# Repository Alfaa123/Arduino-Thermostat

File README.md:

# Arduino-Thermostat

This is a project to create a Arduino (or Arduino compatible) powered home thermostat. Version 2 PCB schematic and design is complete.

# Electrical Design

Version 2 has been updated and upgraded to use many SMD components. The board has shrunk, extra protections added and lots of the lessons learned from V1 were implemented as changes to V2.

## Power Section

This takes the 24v AC from the air handler transformer and rectifies it to create a high voltage DC bus. This is then smoothed and an LM2596 is used as a switching regulator to create a 3.3v supply.

Power for the feather is supplied via the 3.3v pin from the onboard voltage regulator.

The regulator can handle up to 3a of current and would be accurately described as "way overkill" for the power requirements of the low voltage section of this board. However, the LM2596 regulators are so simple and easy to effectively use (thanks TI!) that it was worth the extra cost to just have something "easy."

Because the circuitry in the air handler requires the relays to be switched on with the supplied 24v AC, it is routed down the board to supply the common terminal of the three main relays.

## Relay Drive Section

In order to drive the relays, small logic level MOSFETS are utilized with the feather board outputs acting as gate drivers for the three MOSFETs. The current requirements for the selected relays are very low and can easily be sunk by the selected MOSFETs.

## Inputs and Outputs

An Adafruit Feather HUZZAH ESP8266 will be used to run the thermostat. This was selected because it was cheap, easy to work with and included a WiFi stack (allowing for some internet connected thermostat features in the future). One limitation of the ESP8266 is the extremely limited IO compared to the Arduino Nano of the V1 design. This lead to lots of design challanges, including the use of the onboard ADC for ladder buttons to save IO.

The central feature of the V2 design is the inclusion of a 2.9 inch e-ink display instead of a standard LCD. This high resolution, low power display will be ideal for a thermostat as the display needs minimal updates during normal usage.

## Physical Outline

The physical outline of the board was designed to mimic my current thermostat. No mounting holes are included in the V2 design due to the success of the board edge mount that was used on the V1 design.

## Lessons Learned for V2

- ~~Arduino placement needs to be revised. Currently plugging in the USB cable is impossible without bending a cable and potentially damaging the Arduino. This is the biggest mistake.~~ **fixed on V2 design. USB connector points toward the board edge and is easy to access**
- ~~Screw terminal placement needs to be revised. Currently with the massive spacing, it required me to trim a lot of the insulation off of the 5 conductor cable in order to spread the wires out far enough to reach.~~ **fixed on V2 design. Screw terminals were moved much closer together and should make wiring the thermostat much easier**
- ~~More markings on the front of the PCB to show which screw terminal does what. Currently it requires me to open the schematic and board files to correctly wire the thermostat.~~ **fixed on V2 design. Board markings on the silkscreen should make wiring the thermostat much easier.**
- ~~More work should be done to minimize footprint. Currently, the thermostat is physically very large.~~ **fixed on V2 design. Board outline has shrunk to around 60% of the original size.**
- ~~A larger screen would be nice to fit more information. A dot matrix or OLED would be best.~~ **fixed on V2 design. e-ink display selected as high resolution and low power display.**
- ~~Smaller regulator section and relays would go a long way to making the board shrink.~~ **unchanged on V2 design. However, the capacitors were revised with shorter, higher quality parts, the regulator was changed to a surface mount version and the diode and inductor were swapped with physically smaller versions.**

# Programming

No V2 programming has been written yet.

## Required Libraries

TBD once V2 programming is underway

## Planned Future Development

- PID control or other method for better temperature control.
- Humidistat control mode
- Adjustable circ fan frequency
- Better menu system
- Filtering on the temperature sensor to prevent rapid cycling
- Cycling time limit to prevent compressor damage

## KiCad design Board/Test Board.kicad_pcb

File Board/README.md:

# Arduino-Thermostat

This is a project to create a arduino powered home thermostat. Currently the project is in the electrical design stage. Version 1 PCB schematic and design is complete.

# Electrical Design

The entire project was designed to be through hole for ease of assembly and troubleshooting. Perhaps in the future, a SMD version with a smaller footprint can be made once the electrical design is finalized.

## Power Section

This takes the 24v AC from the air handler transformer and rectifies it to create a higher voltage DC bus. This is then smoothed and an LM2596 is used as a switching regulator to create a 5.0v supply.

Power for the arduino is supplied via the 5v pin from the onboard voltage regulator.

The regulator can handle upto 3a of current and would be accurately described as "way overkill" for the power requirements of the low voltage section of this board. Once V1 is confirmed to be working, a redesign will be carried out that will allow a lower BOM cost and a physical design shrink.

Because the circuitry in the air handler requires the relays to be switched on with the supplied 24v AC, it is routed down the board to supply the common terminal of the three main relays.

## Relay Driver

A L293D Bipolar Motor Driver was chosen because it was readily available in DIP format, worked for the voltages required, had logic level inputs and had built in flyback diodes that allowed for less physical space usage at the expense of a higher BOM cost.

Additionally, due to the extra available output, the supply for the LCD backlight is switched with output 4.

## Inputs and Outputs

An arduino nano will be used to run the thermostat, ample GPIO meant that each physical button could have it's own DIO pin. Additionally, the LCD was able to be run directly in 4 bit parallel mode allowing for lower BOM cost and simpler electrical design.

The DHT11 may be swapped out with a DHT22 as they have the same footprint and the DHT 22 has a wider range of measurement.

## Physical Outline

The physical outline of the board was designed to mimic my current thermostat. 4 mounting holes were provided to allow for either wall mounting or a case.

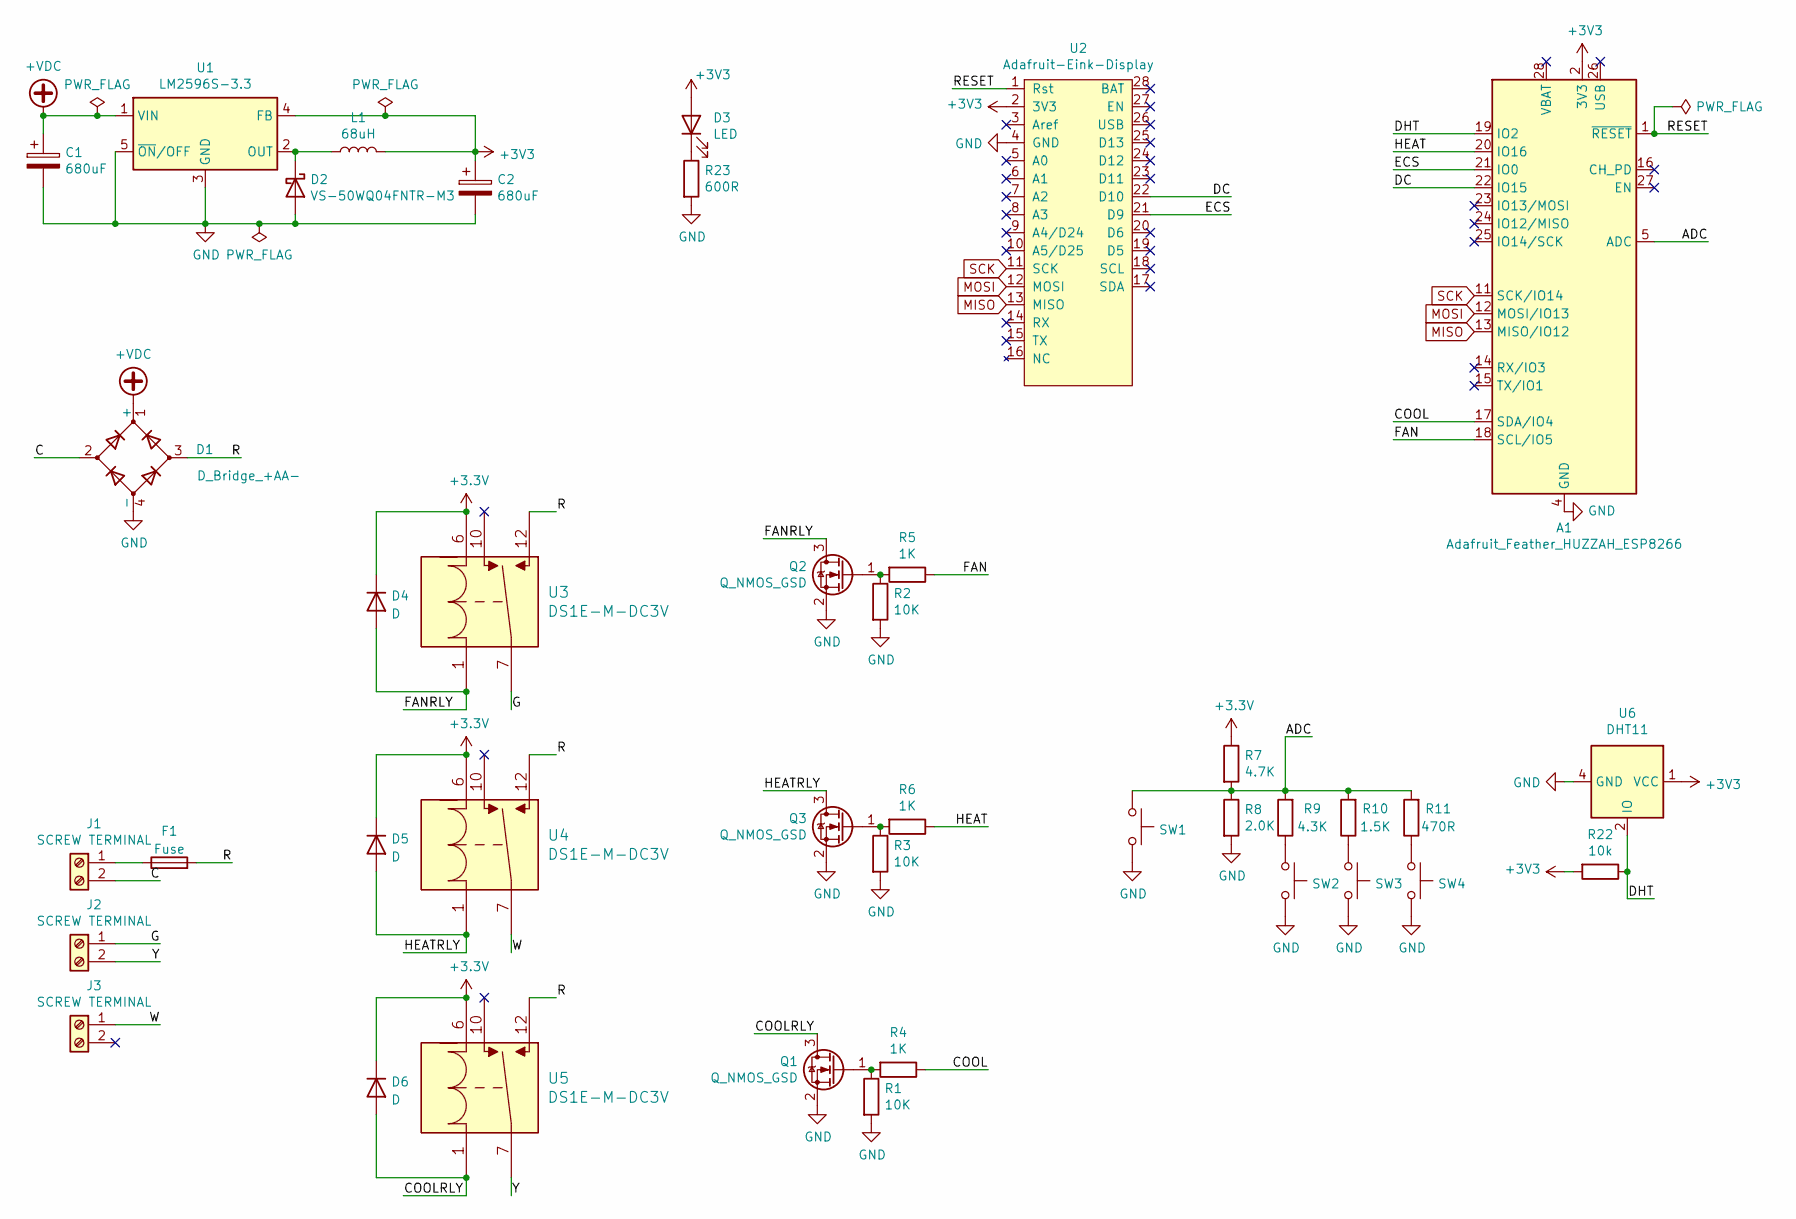
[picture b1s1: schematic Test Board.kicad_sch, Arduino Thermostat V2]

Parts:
A1: Adafruit_Feather_HUZZAH_ESP8266; Adafruit_Feather
C1, C2: 680uF; CP_Radial_D18.0mm_P7.50mm
D1: D_Bridge_+AA-; Diode Bridge 4-SMD
D2: VS-50WQ04FNTR-M3; TO-252-3_TabPin2
D3: LED; LED_1206_3216Metric_Pad1.42x1.75mm_HandSolder
D4, D5, D6: D; D_SMA_Handsoldering
F1: Fuse; Fuseholder_Blade_Mini_Keystone_3568
J1, J2, J3: SCREW TERMINAL; TerminalBlock_Phoenix_MKDS-1,5-2-5.08_1x02_P5.08mm_Horizont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
L1: 68uH; L_Radial_L16.1mm_W16.1mm_Px7.62mm_Py12.70mm_Pulse_LP-44
Q1, Q2, Q3: Q_NMOS_GSD; SOT-23
R1, R2, R3: 10K; R_1206_3216Metric
R4, R5, R6: 1K; R_1206_3216Metric
R7: 4.7K; R_1206_3216Metric
R8: 2.0K; R_1206_3216Metric
R9: 4.3K; R_1206_3216Metric
R10: 1.5K; R_1206_3216Metric
R11: 470R; R_1206_3216Metric
R22: 10k; R_1206_3216Metric
R23: 600R; R_1206_3216Metric
SW1, SW2, SW3, SW4: SW_Push; SW_PUSH_6mm_H5mm
U1: LM2596S-3.3; TO-263-5_TabPin3
U2: Adafruit-Eink-Display; Adafruit-eink-display
U3, U4, U5: DS1E-M-DC3V; DS1E-M-DC5V
U6: DHT11; DHT22-Horizontal

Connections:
+VDC: C1.1, D1.1 (+), U1.1 (VIN)
/ADC: A1.5 (ADC), R7.2, R8.1, R9.2, R10.2, R11.2, SW1.1
/C: D1.2, J1.2
/COOL: A1.17 (SDA/IO4), R4.1
/COOLRLY: D6.2 (A), Q1.3 (D), U5.1
/DC: A1.22 (IO15), U2.22 (D10)
/DHT: A1.19 (IO2), R22.1, U6.2 (IO)
/ECS: A1.21 (IO0), U2.21 (D9)
/FAN: A1.18 (SCL/IO5), R5.1
/FANRLY: D4.2 (A), Q2.3 (D), U3.1
/G: J2.1, U3.7
/HEAT: A1.20 (IO16), R6.1
/HEATRLY: D5.2 (A), Q3.3 (D), U4.1
/R: D1.3, F1.2, U3.12, U4.12, U5.12
/RESET: A1.1 (~RESET), U2.1 (Rst)
/W: J3.1, U4.7
/Y: J2.2, U5.7
GND: A1.4 (GND), C1.2, C2.2, D1.4 (-), D2.2 (A), Q1.2 (S), Q2.2 (S), Q3.2 (S), R1.2, R2.2, R3.2, R8.2, R23.2, SW1.2, SW2.2, SW3.2, SW4.2, U1.3 (GND), U1.5 (~ON/OFF), U2.4 (GND), U6.4 (GND)
MISO: A1.13 (MISO/IO12), U2.13 (MISO)
MOSI: A1.12 (MOSI/IO13), U2.12 (MOSI)
unnamed: D2.1 (K), L1.1, U1.2 (OUT)
unnamed: D3.1 (K), R23.1
unnamed: F1.1, J1.1
unnamed: Q1.1 (G), R1.1, R4.2
unnamed: Q2.1 (G), R2.1, R5.2
unnamed: Q3.1 (G), R3.1, R6.2
unnamed: R9.1, SW2.1
unnamed: R10.1, SW3.1
unnamed: R11.1, SW4.1
SCK: A1.11 (SCK/IO14), U2.11 (SCK)

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
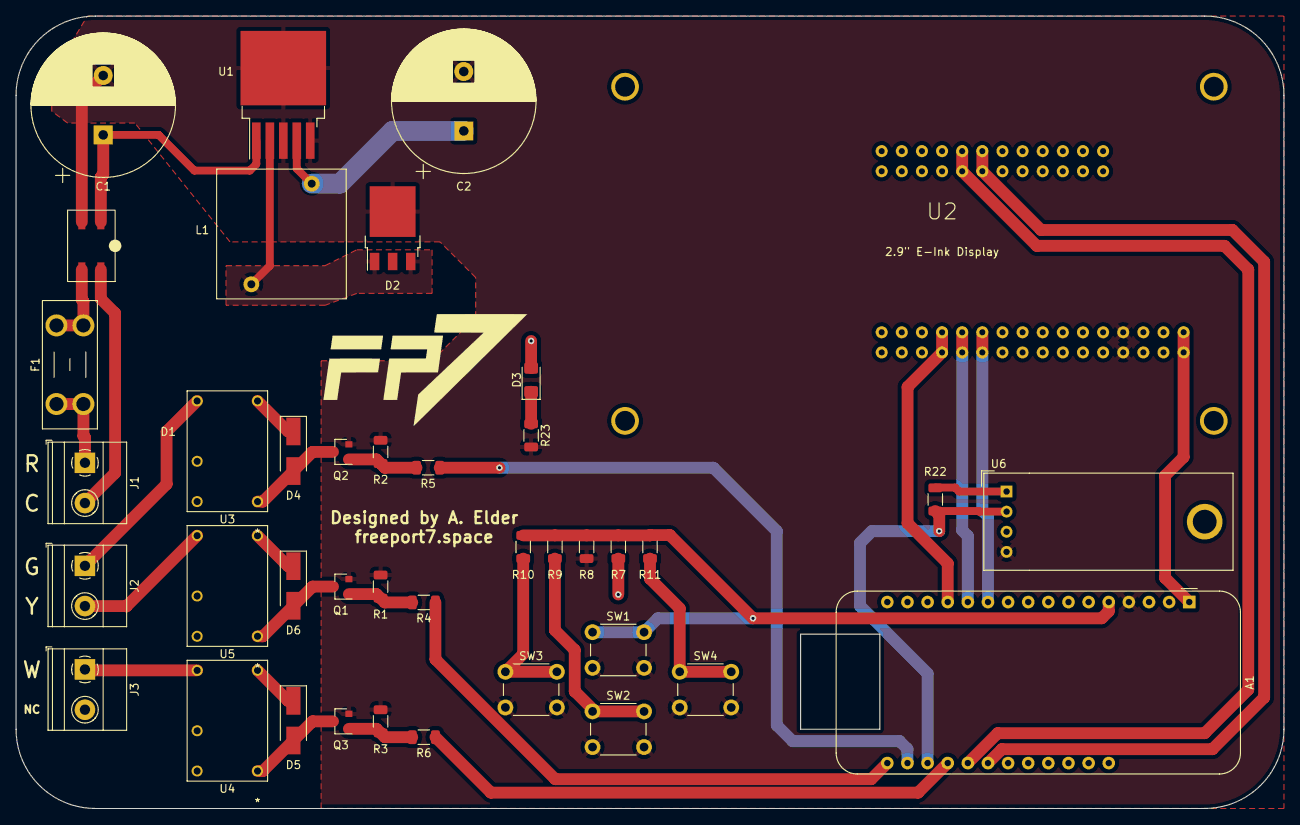
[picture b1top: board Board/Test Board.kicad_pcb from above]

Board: 2 copper layers, 160.0 x 100.0 mm, 40 parts (0 on the bottom side), 31 nets.

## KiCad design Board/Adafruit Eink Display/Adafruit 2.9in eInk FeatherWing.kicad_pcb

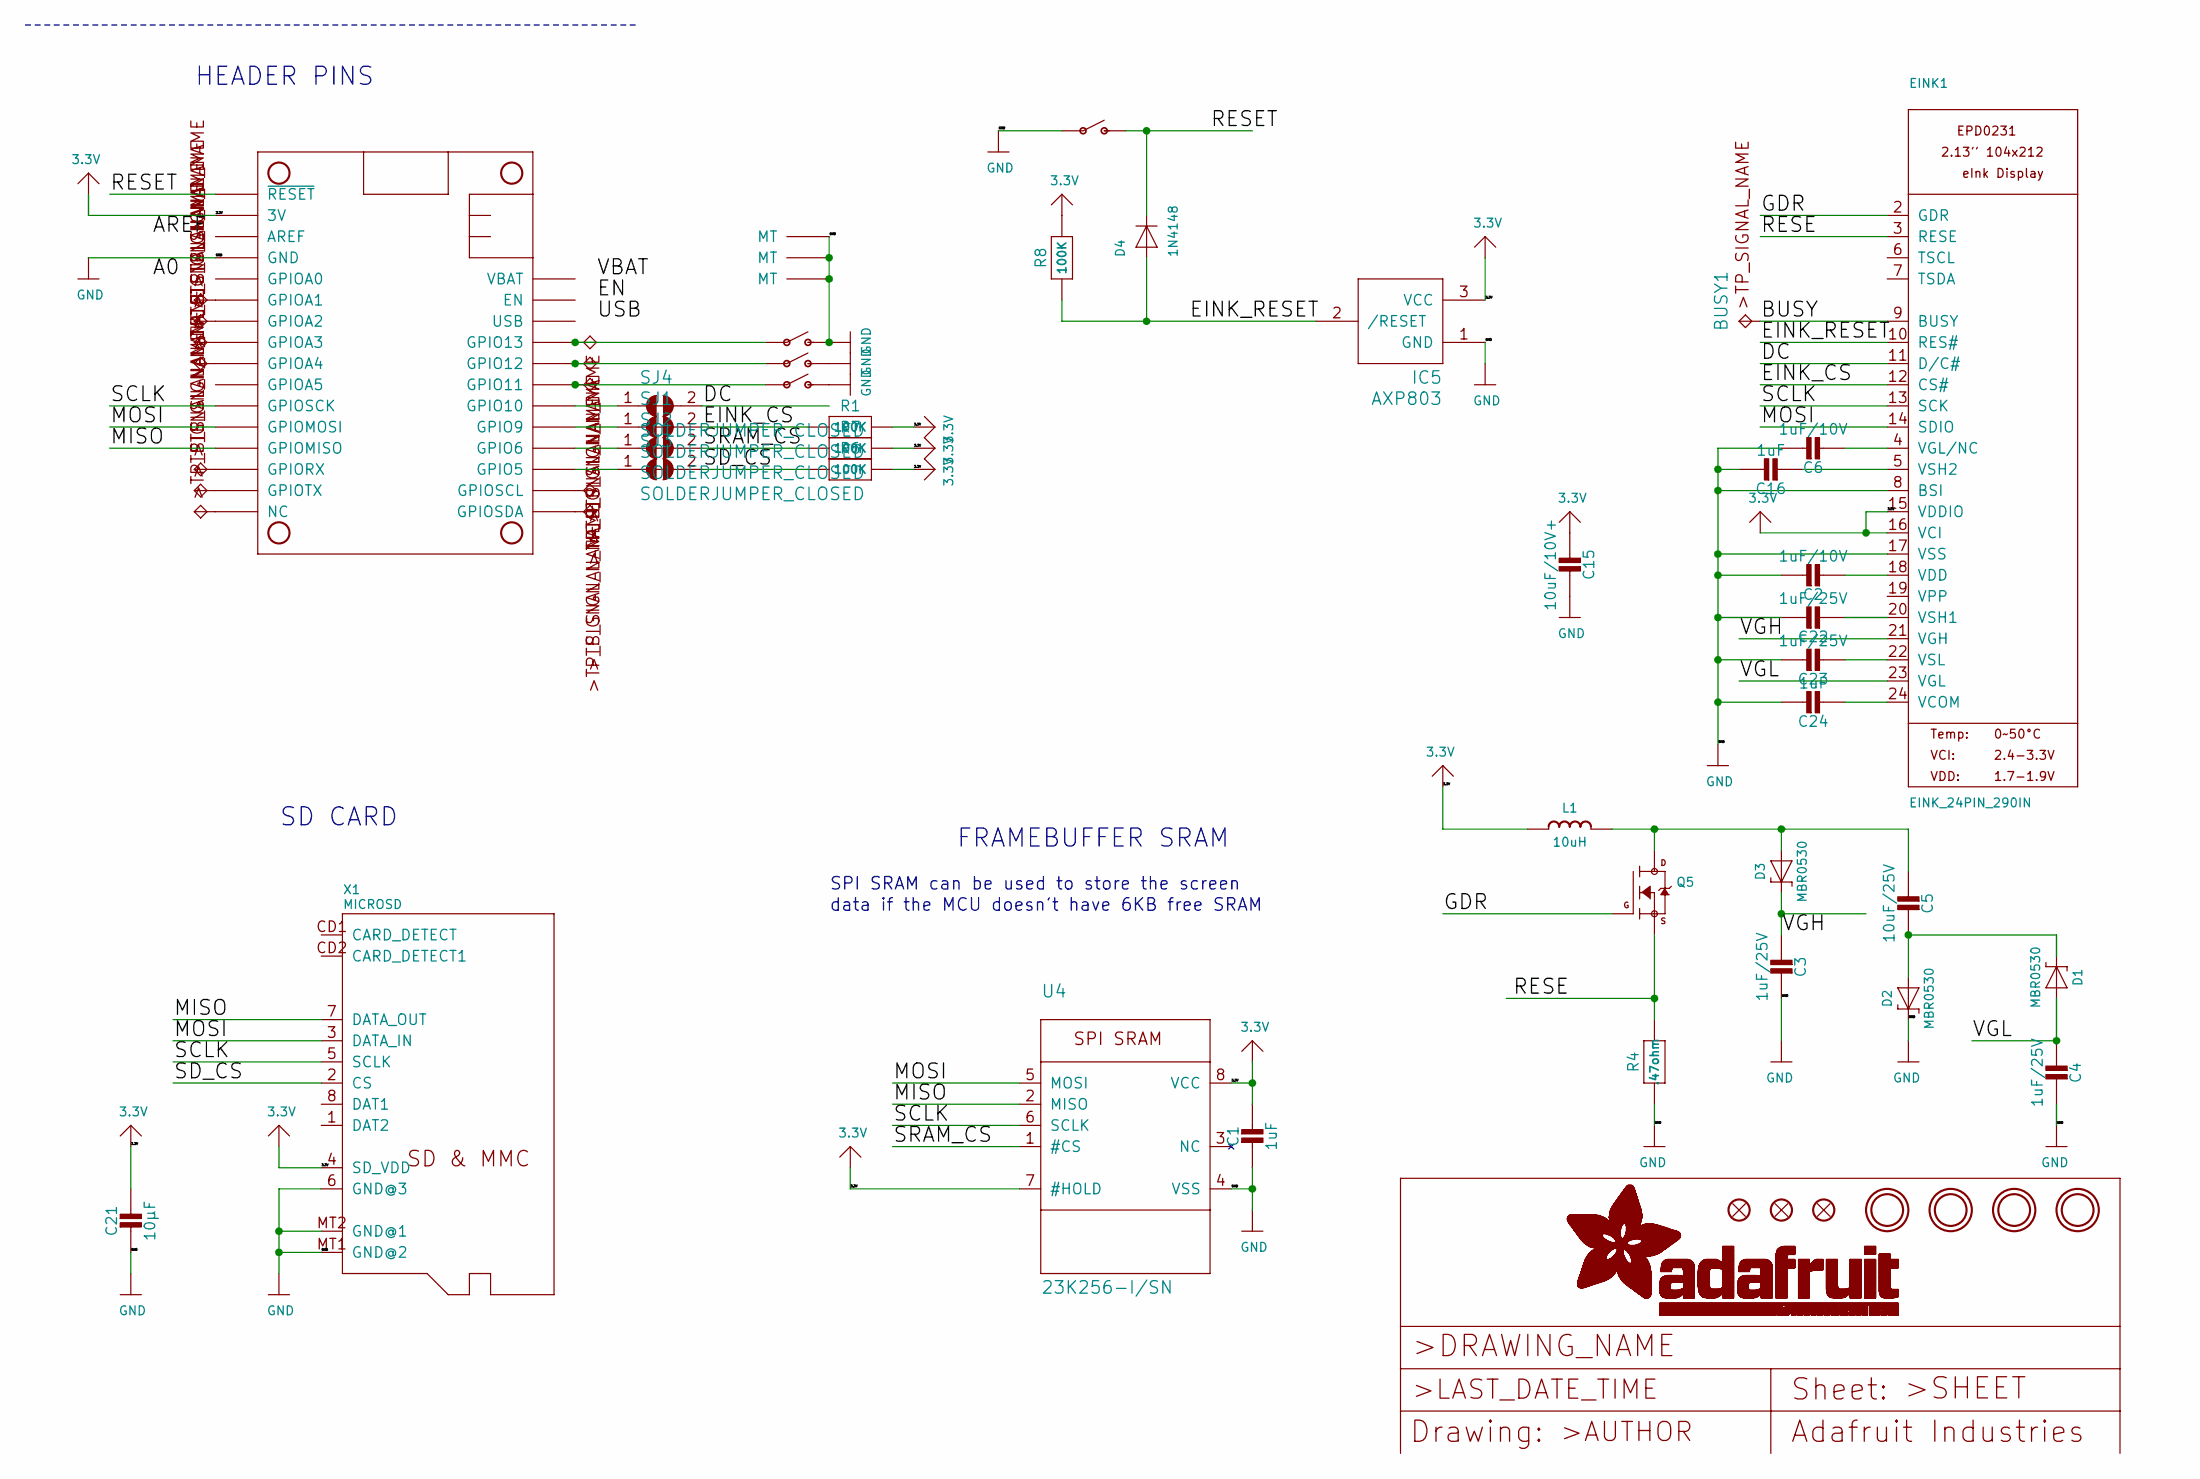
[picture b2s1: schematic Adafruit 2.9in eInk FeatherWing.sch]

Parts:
BUSY1: TPTP15SQ; TP15SQ
C1: 1uF; 0805_10MGAP
C2, C6: 1uF/10V; 0805-NO
C3, C4, C22, C23: 1uF/25V; 0805-NO
C5: 10uF/25V; 0805-NO
C15: 10uF/10V+; 0805-NO
C16, C24: 1uF; 0805-NO
C21: 10µF; 0805-NO
D1, D2, D3: MBR0530; SOD-123
D4: 1N4148; SOD-323F
EINK1: EINK_24PIN_290IN; EINK_290IN
FID1, FID2, FID3: FIDUCIAL_1MM
IC5: AXP803; SOT23
L1: 10uH; INDUCTOR_4X4MM_NR401
MS1: FEATHERWING_SMTDUALNOHOLES; FEATHERWING_SMT_NOHOLES
Q5: IRLML0100; SOT23-3
R1, R6, R7, R8: 100K; 0603-NO
R4: .47ohm; 0805_10MGAP
SJ1, SJ2, SJ3, SJ4: SOLDERJUMPER_CLOSED; SOLDERJUMPER_CLOSEDWIRE
SW1, SW2, SW3, SW4: SWITCH_SPST_TACT_RA; SPST_TACTILE_RA
TP1, TP2, TP3, TP4, TP5, TP6, TP7, TP8, TP9, TP11, TP12, TP13: TPTP15SQ; TP15SQ
U4: 23K256-I/SN; SOIC8_150MIL
U$3, U$4, U$5, U$6: MOUNTINGHOLE2.5; MOUNTINGHOLE_2.5_PLATED
X1: MICROSD

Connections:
3.3V: C1.1, C15.2, C21.1, EINK1.15 (VDDIO), EINK1.16 (VCI), IC5.3 (VCC), L1.P$2 (2), MS1.2 (3V), MS1.2B (3V), R1.2, R6.2, R7.2, R8.2, U4.7 (#HOLD), U4.8 (VCC), X1.4 (SD_VDD)
/BUSY: BUSY1.TP, EINK1.9 (BUSY)
/DC: EINK1.11 (D/C#), SJ4.2
/EINK_CS: EINK1.12 (CS#), R1.1, SJ1.2
/EINK_RESET: D4.A, EINK1.10 (RES#), IC5.2 (/RESET), R8.1
/GDR: EINK1.2 (GDR), Q5.1 (G)
/MISO: MS1.13 (GPIOMISO), MS1.13B (GPIOMISO), U4.2 (MISO), X1.7 (DATA_OUT)
/MOSI: EINK1.14 (SDIO), MS1.12 (GPIOMOSI), MS1.12B (GPIOMOSI), U4.5 (MOSI), X1.3 (DATA_IN)
/RESE: EINK1.3 (RESE), Q5.2 (S), R4.1
/RESET: D4.C, MS1.1 (~RESET), MS1.1B (~RESET), SW3.2 (S)
/SCLK: EINK1.13 (SCK), MS1.11 (GPIOSCK), MS1.11B (GPIOSCK), U4.6 (SCLK), X1.5 (SCLK)
/SD_CS: R6.1, SJ3.2, X1.2 (CS)
/SRAM_CS: R7.1, SJ2.2, U4.1 (#CS)
/VGH: C3.1, D3.C, EINK1.21 (VGH)
/VGL: C4.1, D1.A, EINK1.23 (VGL)
GND: C1.2, C2.1, C3.2, C4.2, C6.1, C15.1, C16.1, C21.2, C22.1, C23.1, C24.1, D2.C, EINK1.8 (BSI), EINK1.17 (VSS), IC5.1 (GND), MS1.4 (GND), MS1.4B (GND), R4.2, SW1.2 (S), SW1.MT1 (MT), SW1.MT2 (MT), SW2.2 (S), SW2.MT1 (MT), SW2.MT2 (MT), SW3.1, SW4.2 (S), SW4.MT1 (MT), SW4.MT2 (MT), U4.4 (VSS), X1.6 (GND@3), X1.MT1 (GND@2), X1.MT2 (GND@1)
unnamed: C2.2, EINK1.18 (VDD)
unnamed: C5.1, D3.A, L1.P$1 (1), Q5.3 (D)
unnamed: C5.2, D1.C, D2.A
unnamed: C6.2, EINK1.4 (VGL/NC)
unnamed: C16.2, EINK1.5 (VSH2)
unnamed: C22.2, EINK1.20 (VSH1)
unnamed: C23.2, EINK1.22 (VSL)
unnamed: C24.2, EINK1.24 (VCOM)
unnamed: MS1.3 (AREF), MS1.3B (AREF)
unnamed: MS1.5 (GPIOA0), MS1.5B (GPIOA0)
unnamed: MS1.6 (GPIOA1), MS1.6B (GPIOA1), TP6.TP
unnamed: MS1.7 (GPIOA2), MS1.7B (GPIOA2), TP7.TP
unnamed: MS1.8 (GPIOA3), MS1.8B (GPIOA3), TP8.TP
unnamed: MS1.9 (GPIOA4), MS1.9B (GPIOA4), TP9.TP
unnamed: MS1.10 (GPIOA5), MS1.10B (GPIOA5)
unnamed: MS1.14 (GPIORX), MS1.14B (GPIORX), TP11.TP
unnamed: MS1.15 (GPIOTX), MS1.15B (GPIOTX), TP12.TP
unnamed: MS1.16 (NC), MS1.16B (NC), TP13.TP
unnamed: MS1.17 (GPIOSDA), MS1.17B (GPIOSDA), TP4.TP
unnamed: MS1.18 (GPIOSCL), MS1.18B (GPIOSCL), TP3.TP
unnamed: MS1.19 (GPIO5), MS1.19B (GPIO5), SJ3.1
unnamed: MS1.20 (GPIO6), MS1.20B (GPIO6), SJ2.1
unnamed: MS1.21 (GPIO9), MS1.21B (GPIO9), SJ1.1
unnamed: MS1.22 (GPIO10), MS1.22B (GPIO10), SJ4.1
unnamed: MS1.23 (GPIO11), MS1.23B (GPIO11), SW1.1, TP1.TP
unnamed: MS1.24 (GPIO12), MS1.24B (GPIO12), SW2.1, TP2.TP
unnamed: MS1.25 (GPIO13), MS1.25B (GPIO13), SW4.1, TP5.TP
unnamed: MS1.26 (USB), MS1.26B (USB)
unnamed: MS1.27 (EN), MS1.27B (EN)
unnamed: MS1.28 (VBAT), MS1.28B (VBAT)

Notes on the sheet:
HEADER PINS
FRAMEBUFFER SRAM
SPI SRAM can be used to store the screen
data if the MCU doesn't have 6KB free SRAM
SD CARD

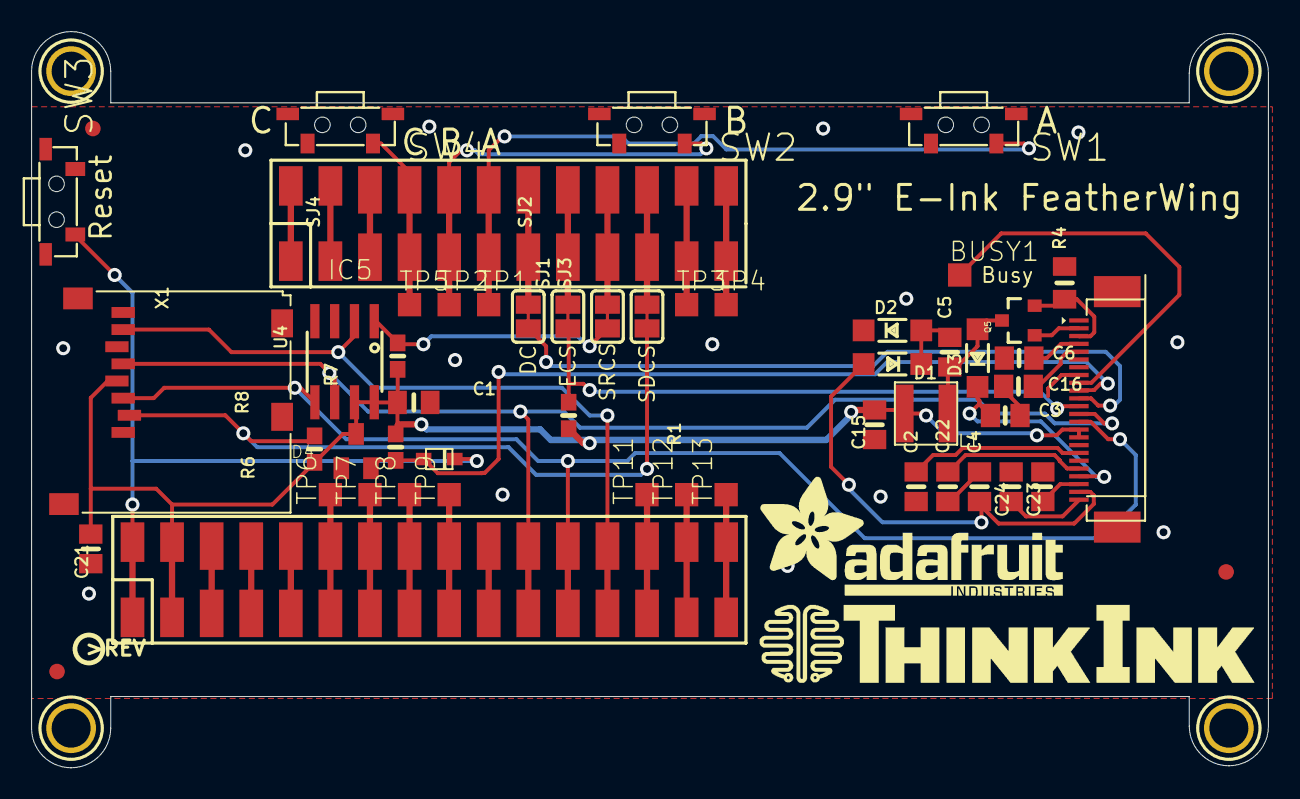
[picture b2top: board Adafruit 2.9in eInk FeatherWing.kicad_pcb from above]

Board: 2 copper layers, 79.4 x 47.2 mm, 59 parts (0 on the bottom side), 46 nets.

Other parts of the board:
U$8: THINKINK_1.25IN
U$9: PCBFEAT-REV-040
U$17: ADAFRUIT_TEXT_20MM

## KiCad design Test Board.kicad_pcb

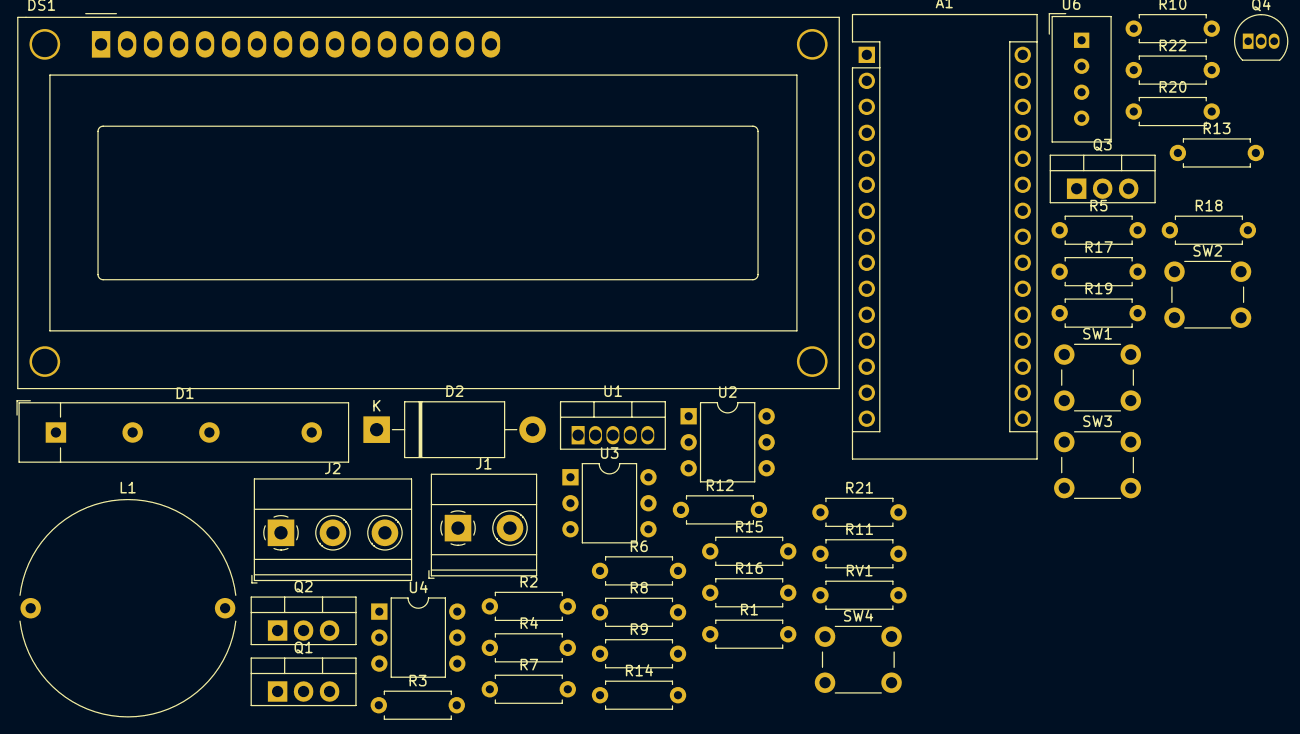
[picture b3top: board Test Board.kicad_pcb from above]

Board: 2 copper layers, 43 parts (0 on the bottom side), 32 nets, no tracks yet.

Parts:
A1: Arduino_Nano_v3.x; Arduino_Nano
D1: B40C5000-3x00A; Diode_Bridge_32.0x5.6x17.0mm_P10.0mm_P7.5mm
D2: MBR360; D_DO-201_P15.24mm_Horizontal
DS1: WC1602A
J1: SCREW TERMINAL; TerminalBlock_Phoenix_MKDS-1,5-2-5.08_1x02_P5.08mm_Horizont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
J2: SCREW TERMINAL; TerminalBlock_Phoenix_MKDS-1,5-3-5.08_1x03_P5.08mm_Horizont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
L1: 330uH; L_Radial_D21.0mm_P19.00mm
Q1, Q2, Q3: BT138-600; TO-220-3_Vertical
Q4: S8050; TO-92_Inline
R1, R2, R3: 560R; R_Axial_DIN0207_L6.3mm_D2.5mm_P7.62mm_Horizontal
R4, R5, R6: 180R; R_Axial_DIN0207_L6.3mm_D2.5mm_P7.62mm_Horizontal
R7, R8, R9: 100R; R_Axial_DIN0207_L6.3mm_D2.5mm_P7.62mm_Horizontal
R10, R11, R12: 33R; R_Axial_DIN0207_L6.3mm_D2.5mm_P7.62mm_Horizontal
R13, R14, R16, R17, R22: 10k; R_Axial_DIN0207_L6.3mm_D2.5mm_P7.62mm_Horizontal
R15: 4.7k; R_Axial_DIN0207_L6.3mm_D2.5mm_P7.62mm_Horizontal
R18, R19, R20, R21: 47k; R_Axial_DIN0207_L6.3mm_D2.5mm_P7.62mm_Horizontal
RV1: 10k; R_Axial_DIN0207_L6.3mm_D2.5mm_P7.62mm_Horizontal
SW1: UP-MJTP1230; SW_PUSH_6mm
SW2: LT-MJTP1230; SW_PUSH_6mm
SW3: DN-MJTP1230; SW_PUSH_6mm
SW4: RT-MJTP1230; SW_PUSH_6mm
U1: LM2575-5.0BT; TO-220-5_Vertical
U2, U3, U4: MOC3012M; DIP-6_W7.62mm
U6: DHT11; Aosong_DHT11_5.5x12.0_P2.54mm

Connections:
+5V: A1.27, DS1.2, DS1.15, L1.2, R13.1, R14.2, R15.1, R17.2, R18.1, R19.1, R20.1, R21.1, R22.2, U1.4, U6.1
+VDC: D1.4, U1.1
/BT: R15.2, R16.2
/C: D1.3, J1.2
/COOL: A1.8, R3.2
/DHT: A1.5, R22.1, U6.2
/FAN: A1.6, R1.2
/G: J2.2, Q1.2, R4.2
/HEAT: A1.7, R2.2
/R: D1.2, J1.1, Q1.1, Q2.1, Q3.1, R7.1, R8.1, R9.1, R10.1, R11.1, R12.1
/SW_DN: A1.10, R20.2, SW3.2
/SW_LT: A1.11, R19.2, SW2.2
/SW_RT: A1.12, R21.2, SW4.2
/SW_UP: A1.9, R18.2, SW1.2
/W: J2.1, Q2.2, R5.2
/Y: J2.3, Q3.2, R6.2
GND: A1.4, A1.29, D1.1, D2.2, DS1.1, Q4.1, RV1.1, SW1.1, SW2.1, SW3.1, SW4.1, U1.3, U1.5, U2.2, U3.2, U4.2, U6.4
unnamed: D2.1, L1.1, U1.2
unnamed: DS1.3, RV1.2
unnamed: DS1.16, Q4.3
unnamed: Q1.3, R4.1, U2.4
unnamed: Q2.3, R5.1, U3.4
unnamed: Q3.3, R6.1, U4.4
unnamed: Q4.2, R16.1
unnamed: R1.1, U2.1
unnamed: R2.1, U3.1
unnamed: R3.1, U4.1
unnamed: R7.2, U2.6
unnamed: R8.2, U3.6
unnamed: R9.2, U4.6
SCL: A1.24, R13.2
SDA: A1.23, R14.1

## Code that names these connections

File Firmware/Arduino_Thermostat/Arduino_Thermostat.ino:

#define backlight_pin 10

#define UP_PIN 6
#define DOWN_PIN 7
#define LEFT_PIN 8
#define RIGHT_PIN 9

#define MAX_MENU_ITEMS 3

#define FAN 3
#define HEAT 4
#define COOL 5

#define HEATING 2
#define COOLING 1

#define CIRC_INTERVAL 1200000

#define LCD_TIMEOUT 10000

#define TEMP_HYSTERESIS 1

#include <AceButton.h>
using namespace ace_button;
#include <LiquidCrystal.h>
#include <BigNums2x2.h>
#include "DHT.h"

void backlight(bool);
void handleButtonEvent(AceButton*, uint8_t, uint8_t);

AceButton buttonUp(UP_PIN);
AceButton buttonDown(DOWN_PIN);
AceButton buttonLeft(LEFT_PIN);
AceButton buttonRight(RIGHT_PIN);

int humidity;
int temperatureArray[3];
int temperature;
char tempIndex = 0;
int setpoint = 75;
bool tempAdjustment = 0;
bool circFanInterval = 0;
bool backlightStatus = 0;
char mode = 0;
char fan = 0;
char menu = 0;
long double updateLCDOldMillis;
long double circFanOldMillis;
long double LCDTimeoutOldMillis;

LiquidCrystal lcd(A1, A0, A5, A4, A3, A2);
DHT dht(2, DHT22);
BigNums2x2 bigNum(TREK);
// the setup function runs once when you press reset or power the board
void setup() {
  pinMode(UP_PIN, INPUT);
  pinMode(DOWN_PIN, INPUT);
  pinMode(LEFT_PIN, INPUT);
  pinMode(RIGHT_PIN, INPUT);

  pinMode(FAN, OUTPUT);
  pinMode(HEAT, OUTPUT);
  pinMode(COOL, OUTPUT);

  ButtonConfig* buttonConfig = ButtonConfig::getSystemButtonConfig();
  buttonConfig->setEventHandler(handleButtonEvent);
  buttonConfig->setFeature(ButtonConfig::kFeatureClick);


  //Serial.begin(9600);
  pinMode(backlight_pin, OUTPUT);
  lcd.begin(16, 2);
  dht.begin();
  for (int x=0;x<3;x++){
  temperatureArray[x] = dht.readTemperature(true);
  }
  backlight(1);
  LCDTimeoutOldMillis = millis();
}

// the loop function runs over and over again forever
void loop() {
  buttonUp.check();
  buttonDown.check();
  buttonLeft.check();
  buttonRight.check();

if  (millis() - LCDTimeoutOldMillis > LCD_TIMEOUT){
  backlight(0);
  menu = 0;
}
else {backlight(1);}
  
  if (millis() - updateLCDOldMillis > 10000) {
    updateDHT();
    printTemp();
    printMenu(menu);
    updateTempControl();
    updateFanControl();
    updateLCDOldMillis = millis();
  }
}

void backlight(bool direction) {
  if (backlightStatus ^ direction){
  for (int x = 0; x < 255; x++) {
    delay(2);
    if (direction) {
      backlightStatus = 1;
      analogWrite(10, x);
    }
    else {
      backlightStatus = 0;
      analogWrite(10, 260 - x);
    }
  }
  }

}

void printTemp() {
  bigNum.print(temperature, 2, 11, ' ');
}

void updateDHT() {
  temperatureArray[tempIndex] = dht.readTemperature(true);
  tempIndex++;
  if (tempIndex > 2){tempIndex = 0;}
  temperature = ((temperatureArray[0] + temperatureArray[1] + temperatureArray[2])/3);
  humidity = dht.readHumidity();
}

void printMenu(char menuNum) {
  lcd.setCursor(0, 0);
  printMenuItem(menuNum);
  lcd.setCursor(0, 1);
  if (menuNum < MAX_MENU_ITEMS) {
    printMenuItem(menuNum + 1);
  }
  else {
    lcd.print("Ver. 0.8 ");
    //printMenuItem(0);
  }
}

void printMenuItem(char itemNum) {
  switch (itemNum) {
    case 0:
      lcd.print("Humid:");
      lcd.print(humidity);
      lcd.print("% ");
      break;
    case 1:
      lcd.print("Setpt:");
      if (mode == 0){lcd.print("OFF");}
      else if (mode == COOLING){lcd.print("C");
      lcd.print(setpoint);}
      else if (mode == HEATING){lcd.print("H");
      lcd.print(setpoint);}
      lcd.print(" ");
      break;
    case 2:
      lcd.print("Mode:");
      switch (mode) {
        case 0:
          lcd.print("OFF ");
          break;
        case COOLING:
          lcd.print("COOL");
          break;
        case HEATING:
          lcd.print("HEAT");
          break;
      }
      break;
    case 3:
      lcd.print("Fan:");
      switch (fan) {
        case 0:
          lcd.print("AUTO ");
          break;
        case 1:
          lcd.print("ON   ");
          break;
        case 2:
          lcd.print("CIRC ");
          break;
      }
      break;
  }
}

void updateTempControl() {
  switch (mode) {
    case 0:
      digitalWrite(HEAT, LOW);
      digitalWrite(COOL, LOW);
      tempAdjustment = 0;
      break;
    case COOLING:
      if (setpoint < temperature - TEMP_HYSTERESIS) {
        tempAdjustment = 1;
        digitalWrite(COOL, HIGH);
      }
      else if (setpoint > temperature + TEMP_HYSTERESIS) {
        tempAdjustment = 0;
        digitalWrite(COOL, LOW);
      }
      break;
    case HEATING:
      if (setpoint > temperature + TEMP_HYSTERESIS) {
        tempAdjustment = 1;
        digitalWrite(HEAT, HIGH);
      }
      else if (setpoint < temperature - TEMP_HYSTERESIS) {
        tempAdjustment = 0;
        digitalWrite(HEAT, LOW);
      }
      break;
  }
}

void updateFanControl() {
  switch (fan) {
      if (tempAdjustment) {
        digitalWrite(FAN, HIGH);
      }
      else {
      case 0:
        digitalWrite(FAN, LOW);
        circFanInterval = 0;
        break;
      case 1:
        digitalWrite(FAN, HIGH);
        circFanInterval = 0;
        break;
      case 2:
        if (millis() - circFanOldMillis > CIRC_INTERVAL) {
          circFanInterval = !circFanInterval;
          circFanOldMillis = millis();
        }
        digitalWrite(FAN, circFanInterval);
        break;
      }
  }


}

void handleButtonEvent(AceButton* button, uint8_t eventType, uint8_t buttonState) {

LCDTimeoutOldMillis = millis();

  switch (eventType) {
    case AceButton::kEventPressed:
      break;
    case AceButton::kEventReleased:
      break;
    case AceButton::kEventClicked:
      switch (button->getPin()) {
        case UP_PIN:
          menu = menu - 1;
          if (menu < 0) {
            menu = 0;
          }
          printMenu(menu);
          break;
        case DOWN_PIN:
          menu++;
          if (menu > MAX_MENU_ITEMS) {
            menu = MAX_MENU_ITEMS;
          }
          printMenu(menu);
          break;
        case LEFT_PIN:
          switch (menu) {
            case 0:
              break;
            case 1:
              setpoint--;
              if (setpoint < 50) {
                setpoint = 50;
              }
              break;
            case 2:
              mode--;
              if (mode < 0) {
                mode = 0;
              }
              break;
            case 3:
              fan--;
              if (fan < 0) {
                fan = 0;
              }
              break;
          }
          printMenu(menu);
          break;
        case RIGHT_PIN:
          switch (menu) {
            case 0:
              break;
            case 1:
              setpoint++;
              if (setpoint > 90) {
                setpoint = 90;
              }
              break;
            case 2:
              mode++;
              if (mode > 2) {
                mode = 2;
              }
              break;
            case 3:
              fan++;
              if (fan > 2) {
                fan = 2;
              }
              break;
          }
          printMenu(menu);
          break;


      }
      break;
  }
}

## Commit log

2021-08-13 Added Board libs
2021-08-14 Finished Schematic
2021-08-15 Added BOM
2021-08-22 Finished Board Layout
2021-09-06 Updated documentation
2021-09-06 Update fp-info-cache
2021-09-13 Started working on firmware
2021-11-07 First Release Working Firmware
2021-11-07 Updated folder structure
2021-11-08 Add temp averaging and LCD timeout
2021-11-08 Updated Version display
2021-11-12 Added some features
2021-11-13 Begin the process of a design shrink
2021-12-05 Started re-engineering board
2022-01-14 Added E-Ink Display files
    Started making E-Ink Display footprints
2022-01-23 Finished E-Ink Footprint
2022-01-24 Added Feather Symbol
2022-02-08 Continued E-Ink display transition
2022-02-16 Finish Schematic for new PCB
2022-02-16 Added KiCad Footprint for Feather
2022-07-06 More changes for surface mount design
2022-07-08 Continue V2 Design
2022-07-09 Continue board layout for v2 design
2022-07-12 Finished board layout, updated readme
2022-07-16 Started E-Ink interface programming

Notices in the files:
parts and their libraries:
Copyright 2021 Accelerated Designs. All rights reserved.
